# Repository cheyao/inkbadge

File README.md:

# Undercity + Github badges

Official badges for undercity (Hackathon @ Github HQ, https://highway.hackclub.com/)

Find the firmware [here](https://github.com/espcaa/undercity-lanyard)! (Start made by me, finished by spc & mpk :D)

Specs:
- 4x User buttons
- RP2350A
- Big big flash
- Super cool pcie connector
- Working firmware 
- Onboard eink module
- 6 neopixels go flash flash
- Pretty art by bnuuuuyguy!
- Awesome artline by acon (@acornitum)
- Check out pcb online [here](https://kicanvas.org/?github=https%3A%2F%2Fgithub.com%2Fcheyao%2Finkbadge%2Ftree%2Fmain%2Fhardware%2Finkbadge)

Additional battery mode avaliable! (Explosions not included this time)

Solder a lipo onto the central holes on top of the buttons - left is V+ right is GND

Licensed under Solderpad license

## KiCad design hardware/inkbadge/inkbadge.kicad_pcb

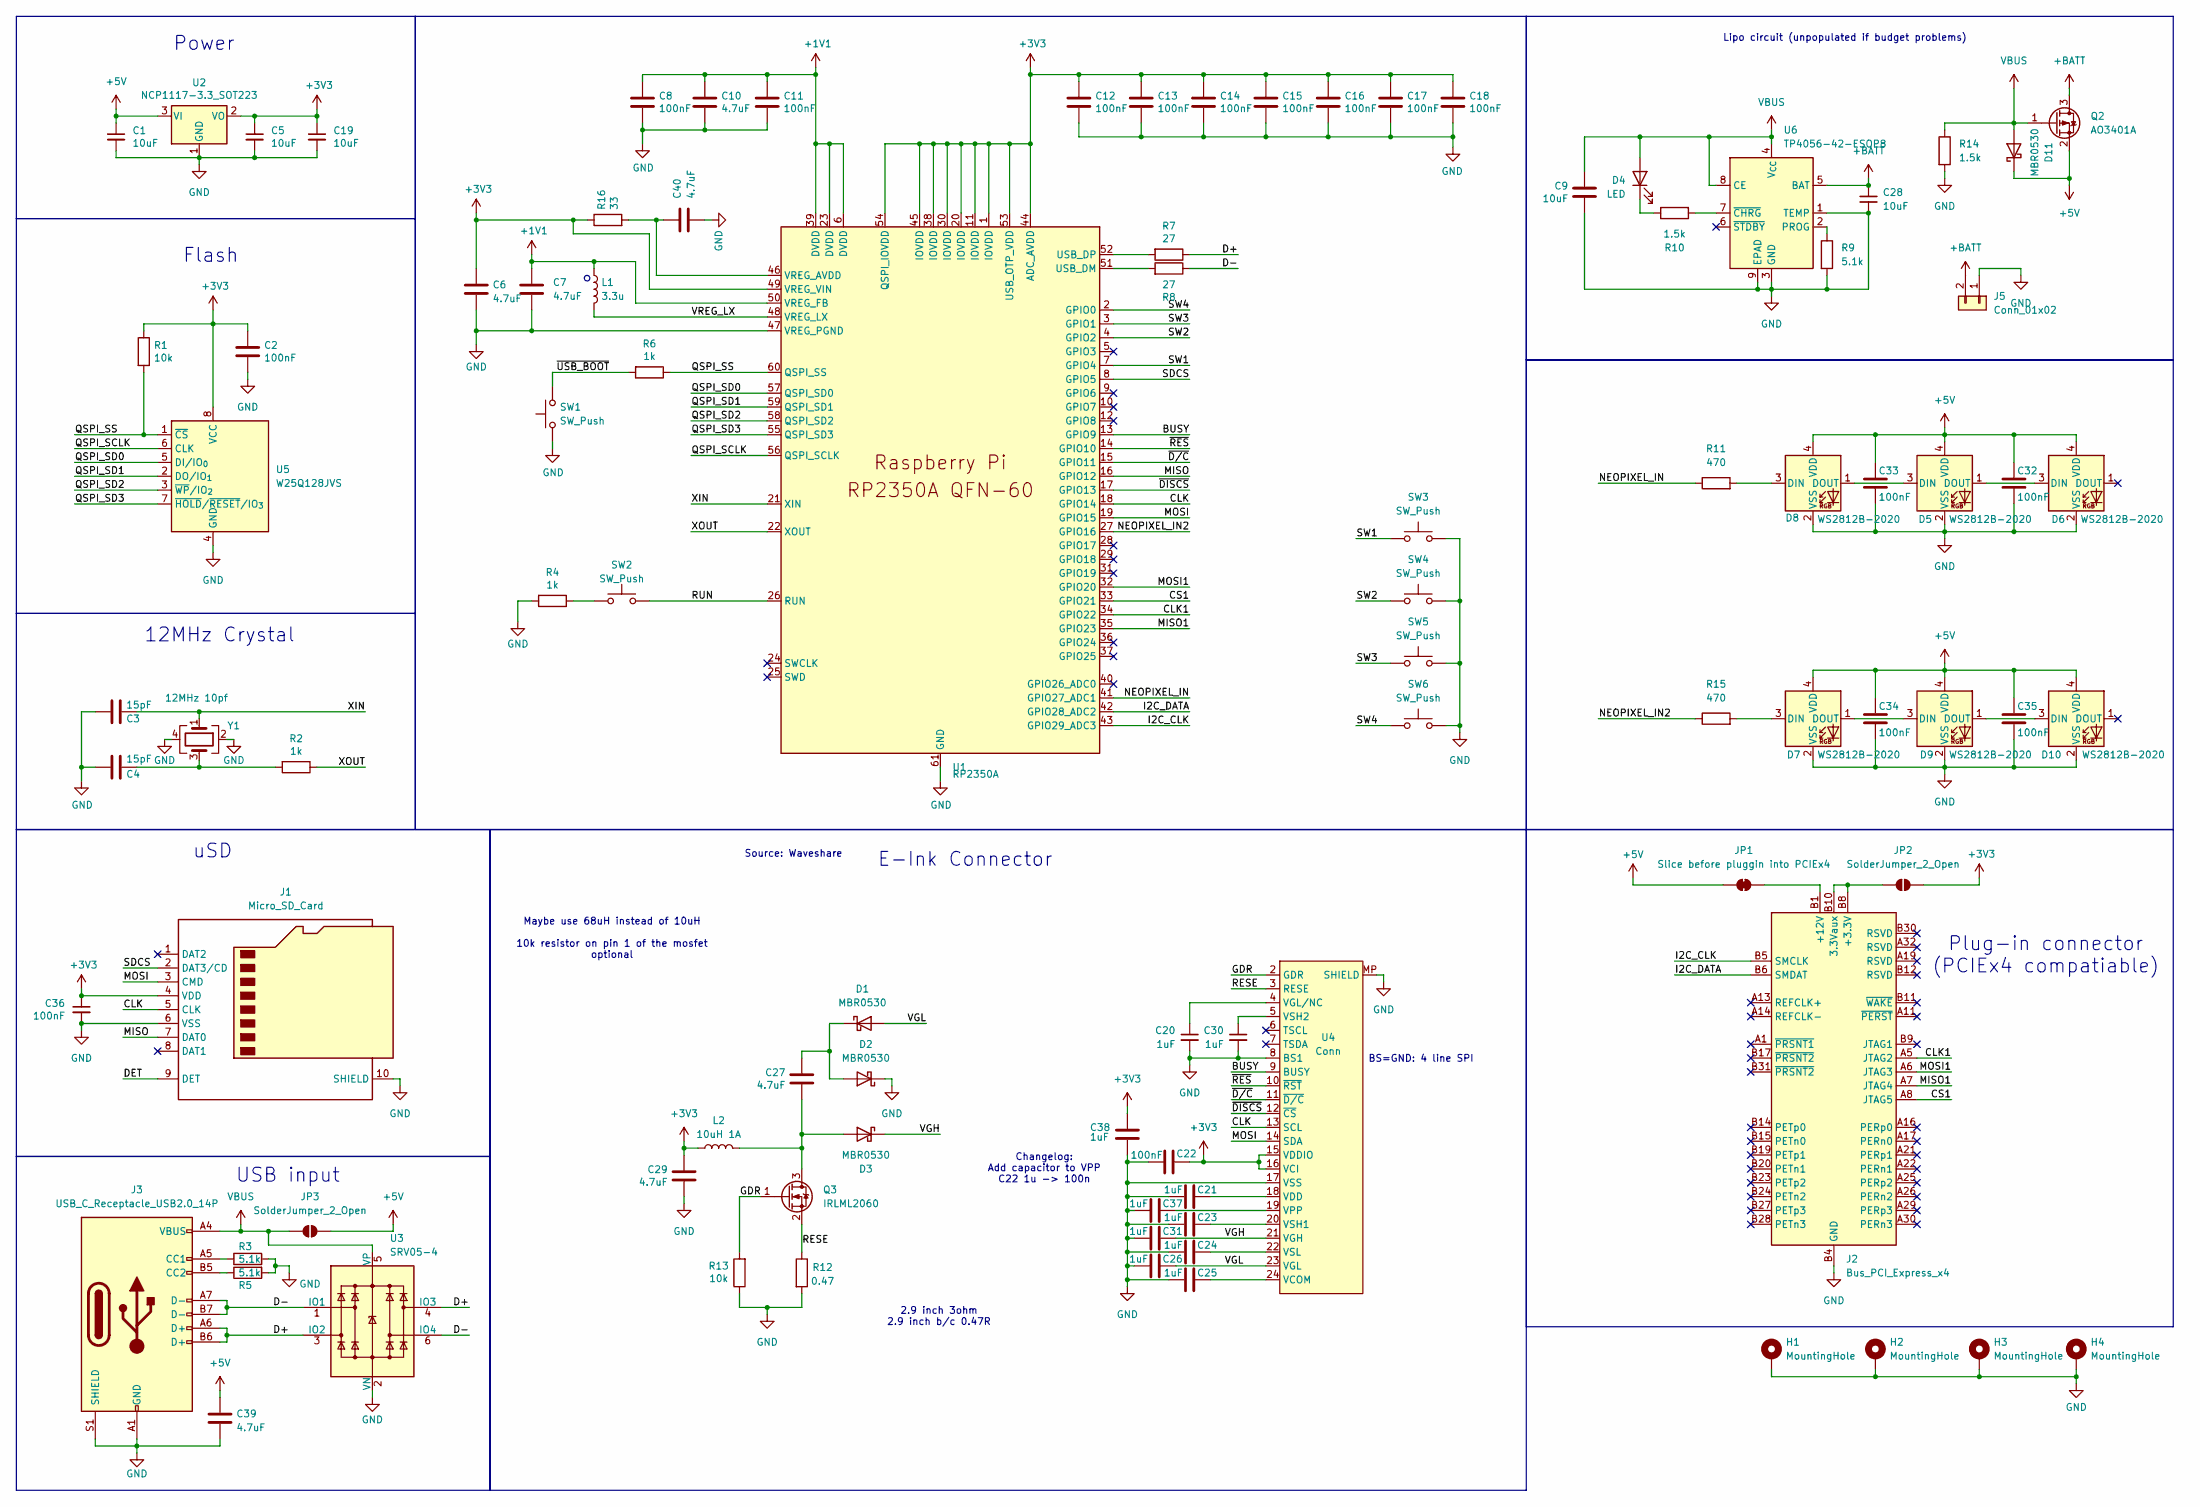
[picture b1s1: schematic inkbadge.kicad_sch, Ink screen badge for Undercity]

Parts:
C1, C5, C9, C19, C28: 10uF; C_0603_1608Metric; LCSC Part # C19702
C2, C8, C11, C12, C13, C14, C15, C16, C17, C18, C22, C32, C33, C34, C35, C36: 100nF; C_0402_1005Metric; LCSC Part # C1525
C3, C4: 15pF; C_0402_1005Metric; LCSC Part # C1548
C6, C7, C10, C40: 4.7uF; C_0402_1005Metric; LCSC Part # C23733
C20, C21, C23, C24, C25, C26, C30, C31, C37, C38: 1uF; C_0402_1005Metric; LCSC Part # C52923
C27, C29, C39: 4.7uF; C_0603_1608Metric; LCSC Part # C69335
D1, D2, D3, D11: MBR0530; D_SOD-123; LCSC Part # C5204746
D4: LED; LED_0603_1608Metric; LCSC Part # C2286
D5, D6, D7, D8, D9, D10: WS2812B-2020; LED_WS2812B-2020_PLCC4_2.0x2.0mm; LCSC Part # C5349955
H1, H2, H3, H4: MountingHole; MountingHole_2.2mm_M2_Pad_Via
J1: Micro_SD_Card; SDCardlcsc; LCSC Part # C5454948
J2: Bus_PCI_Express_x4; BUS_PCIexpress_x4
J3: USB_C_Receptacle_USB2.0_14P; USB_C_Receptacle_GCT_USB4105-xx-A_16P_TopMnt_Horizontal; LCSC Part # C2765186
J5: Conn_01x02; PinHeader_1x02_P2.54mm_Vertical
JP1: Slice before pluggin into PCIEx4; SolderJumper-2_P1.3mm_Bridged_RoundedPad1.0x1.5mm
JP2, JP3: SolderJumper_2_Open; SolderJumper-2_P1.3mm_Open_RoundedPad1.0x1.5mm
L1: 3.3u; L_pol_2016; LCSC Part # C42411119
L2: 10uH 1A; L_APV_ANR4018; LCSC Part # C167808
Q2: AO3401A; SOT-23; LCSC Part # C15127
Q3: IRLML2060; SOT-23; LCSC Part # C5122027
R1, R13: 10k; R_0402_1005Metric; LCSC Part # C25744
R2, R4, R6: 1k; R_0402_1005Metric; LCSC Part # C11702
R3, R5, R9: 5.1k; R_0402_1005Metric; LCSC Part # C25905
R7, R8: 27; R_0402_1005Metric; LCSC Part # C25105
R10, R14: 1.5k; R_0402_1005Metric; LCSC Part # C25867
R11, R15: 470; R_0402_1005Metric; LCSC Part # C25117
R12: 0.47; R_0402_1005Metric; LCSC Part # C3017627
R16: 33; R_0402_1005Metric; LCSC Part # C25105
SW1, SW2, SW3, SW4, SW5, SW6: SW_Push; SW_Push_SPST_TSA016; LCSC Part # C2888430
U1: RP2350A; QFN-60-1EP_7x7mm_P0.4mm_EP3.4x3.4mm_ThermalVias; LCSC Part # C42411118
U2: NCP1117-3.3_SOT223; SOT-223-3_TabPin2; LCSC Part # C6186
U3: SRV05-4; SOT-23-6; LCSC Part # C85364
U4: Conn; LCSC_1x24-1MP_P0.5mm_Horizontal; LCSC Part # C262567
U5: W25Q128JVS; SOIC-8_5.3x5.3mm_P1.27mm; LCSC Part # C97521
U6: TP4056-42-ESOP8; SOP-8_3.9x4.9mm_P1.27mm-TP; LCSC Part # C16581
Y1: 12MHz 10pf; Crystal_SMD_3225-4Pin_3.2x2.5mm; LCSC Part # C20625731

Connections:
+1V1: C7.1, C8.1, C10.1, C11.1, L1.1, U1.6 (DVDD), U1.23 (DVDD), U1.39 (DVDD), U1.50 (VREG_FB)
+3V3: C2.1, C5.1, C6.1, C12.1, C13.1, C14.1, C15.1, C16.1, C17.1, C18.1, C19.1, C22.1, C29.1, C36.1, C38.1, J1.4 (VDD), JP2.2 (B), L2.1, R1.1, R16.1, U1.1 (IOVDD), U1.11 (IOVDD), U1.20 (IOVDD), U1.30 (IOVDD), U1.38 (IOVDD), U1.44 (ADC_AVDD), U1.45 (IOVDD), U1.49 (VREG_VIN), U1.53 (USB_OTP_VDD), U1.54 (QSPI_IOVDD), U2.2 (VO), U4.15 (VDDIO), U4.16 (VCI), U5.8 (VCC)
+5V: C1.1, C32.1, C33.1, C34.1, C35.1, C39.1, D5.4 (VDD), D6.4 (VDD), D7.4 (VDD), D8.4 (VDD), D9.4 (VDD), D10.4 (VDD), D11.1 (K), JP1.1 (A), JP3.2 (B), Q2.2 (S), U2.3 (VI)
+BATT: C28.1, J5.2, Q2.3 (D), U6.5 (BAT)
/BUSY: U1.13 (GPIO9), U4.9 (BUSY)
/CLK: J1.5 (CLK), U1.18 (GPIO14), U4.13 (SCL)
/CLK1: J2.A5 (JTAG2), U1.34 (GPIO22)
/CS1: J2.A8 (JTAG5), U1.33 (GPIO21)
/D+: J3.A6 (D+), J3.B6 (D+), R7.1, U3.3 (IO2), U3.4 (IO3)
/D-: J3.A7 (D-), J3.B7 (D-), R8.1, U3.1 (IO1), U3.6 (IO4)
/DET: J1.9 (DET)
/GDR: Q3.1 (G), R13.2, U4.2 (GDR)
/I2C_CLK: J2.B5 (SMCLK), U1.43 (GPIO29_ADC3)
/I2C_DATA: J2.B6 (SMDAT), U1.42 (GPIO28_ADC2)
/MISO: J1.7 (DAT0), U1.16 (GPIO12)
/MISO1: J2.A7 (JTAG4), U1.35 (GPIO23)
/MOSI: J1.3 (CMD), U1.19 (GPIO15), U4.14 (SDA)
/MOSI1: J2.A6 (JTAG3), U1.32 (GPIO20)
/NEOPIXEL_IN: R11.1, U1.41 (GPIO27_ADC1)
/NEOPIXEL_IN2: R15.1, U1.27 (GPIO16)
/QSPI_SCLK: U1.56 (QSPI_SCLK), U5.6 (CLK)
/QSPI_SD0: U1.57 (QSPI_SD0), U5.5 (DI/IO_{0})
/QSPI_SD1: U1.59 (QSPI_SD1), U5.2 (DO/IO_{1})
/QSPI_SD2: U1.58 (QSPI_SD2), U5.3 (~WP/IO_{2})
/QSPI_SD3: U1.55 (QSPI_SD3), U5.7 (~HOLD/~RESET/IO_{3})
/QSPI_SS: R1.2, R6.1, U1.60 (QSPI_SS), U5.1 (~CS)
/RESE: Q3.2 (S), R12.1, U4.3 (RESE)
/RUN: SW2.2, U1.26 (RUN)
/SDCS: J1.2 (DAT3/CD), U1.8 (GPIO5)
/SW1: SW3.1, U1.7 (GPIO4)
/SW2: SW4.1, U1.4 (GPIO2)
/SW3: SW5.1, U1.3 (GPIO1)
/SW4: SW6.1, U1.2 (GPIO0)
/VGH: C31.1, D3.1 (K), U4.21 (VGH)
/VGL: C26.1, D1.2 (A), U4.23 (VGL)
/VREG_LX: L1.2, U1.48 (VREG_LX)
/XIN: C3.1, U1.21 (XIN), Y1.1
/XOUT: R2.1, U1.22 (XOUT)
/~DISCS: U1.17 (GPIO13), U4.12 (~CS)
/~D/C: U1.15 (GPIO11), U4.11 (~D/C)
/~RES: U1.14 (GPIO10), U4.10 (~RST)
/~USB_BOOT: R6.2, SW1.2
GND: C1.2, C2.2, C3.2, C4.2, C5.2, C6.2, C7.2, C8.2, C9.2, C10.2, C11.2, C12.2, C13.2, C14.2, C15.2, C16.2, C17.2, C18.2, C19.2, C20.2, C21.2, C22.2, C23.2, C24.2, C25.2, C26.2, C28.2, C29.2, C30.2, C31.2, C32.2, C33.2, C34.2, C35.2, C36.2, C37.2, C38.2, C39.2, C40.2, D2.1 (K), D5.2 (VSS), D6.2 (VSS), D7.2 (VSS), D8.2 (VSS), D9.2 (VSS), D10.2 (VSS), H1.1, H2.1, H3.1, H4.1, J1.6 (VSS), J1.10 (SHIELD), J2.A4 (GND), J2.A12 (GND), J2.A15 (GND), J2.A18 (GND), J2.A20 (GND), J2.A23 (GND), J2.A24 (GND), J2.A27 (GND), J2.A28 (GND), J2.A31 (GND), J2.B4 (GND), J2.B7 (GND), J2.B13 (GND), J2.B16 (GND), J2.B18 (GND), J2.B21 (GND), J2.B22 (GND), J2.B25 (GND), J2.B26 (GND), J2.B29 (GND), J2.B32 (GND), J3.A1 (GND), J3.A12 (GND), J3.B1 (GND), J3.B12 (GND), J3.S1 (SHIELD), J5.1, R3.2, R4.2, R5.2, R9.2, R12.2, R13.1, R14.2, SW1.1, SW3.2, SW4.2, SW5.2, SW6.2, U1.47 (VREG_PGND), U1.61 (GND), U2.1 (GND), U3.2 (VN), U4.8 (BS1), U4.17 (VSS), U4.MP (SHIELD), U5.4 (GND), U6.1 (TEMP), U6.3 (GND), U6.9 (EPAD), Y1.2, Y1.4
unnamed: C4.1, R2.2, Y1.3
unnamed: C27.1, D1.1 (K), D2.2 (A)
unnamed: C27.2, D3.2 (A), L2.2, Q3.3 (D)
unnamed: D4.1 (K), R10.1
unnamed: D5.3 (DIN), D8.1 (DOUT)
unnamed: D5.1 (DOUT), D6.3 (DIN)
unnamed: D7.3 (DIN), R15.2
unnamed: D7.1 (DOUT), D9.3 (DIN)
unnamed: D8.3 (DIN), R11.2
unnamed: D9.1 (DOUT), D10.3 (DIN)
unnamed: J2.A9 (+3.3V), J2.A10 (+3.3V), J2.B8 (+3.3V), J2.B10 (3.3Vaux), JP2.1 (A)
unnamed: J3.A5 (CC1), R3.1
unnamed: J3.B5 (CC2), R5.1
unnamed: J2.A2 (+12V), J2.A3 (+12V), J2.B1 (+12V), J2.B2 (+12V), J2.B3 (+12V), JP1.2 (B)
unnamed: R4.1, SW2.1
unnamed: R8.2, U1.51 (USB_DM)
unnamed: R7.2, U1.52 (USB_DP)
unnamed: C40.1, R16.2, U1.46 (VREG_AVDD)
unnamed: C25.1, U4.24 (VCOM)
unnamed: C21.1, U4.18 (VDD)
unnamed: C20.1, U4.4 (VGL/NC)
unnamed: C37.1, U4.19 (VPP)
unnamed: C23.1, U4.20 (VSH1)
unnamed: C30.1, U4.5 (VSH2)
unnamed: C24.1, U4.22 (VSL)
unnamed: R9.1, U6.2 (PROG)
unnamed: R10.2, U6.7 (~CHRG)
VBUS: C9.1, D4.2 (A), D11.2 (A), J3.A4 (VBUS), J3.A9 (VBUS), J3.B4 (VBUS), J3.B9 (VBUS), JP3.1 (A), Q2.1 (G), R14.1, U3.5 (VP), U6.4 (V_{CC}), U6.8 (CE)

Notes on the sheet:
USB input
Maybe use 68uH instead of 10uH 10k resistor on pin 1 of the mosfet optional
Plug-in connector (PCIEx4 compatiable)
Changelog: Add capacitor to VPP C22 1u -> 100n
Lipo circuit (unpopulated if budget problems)
Flash
2.9 inch 3ohm 2.9 inch b/c 0.47R
BS=GND: 4 line SPI
uSD
Source: Waveshare
12MHz Crystal
Power
E-Ink Connector

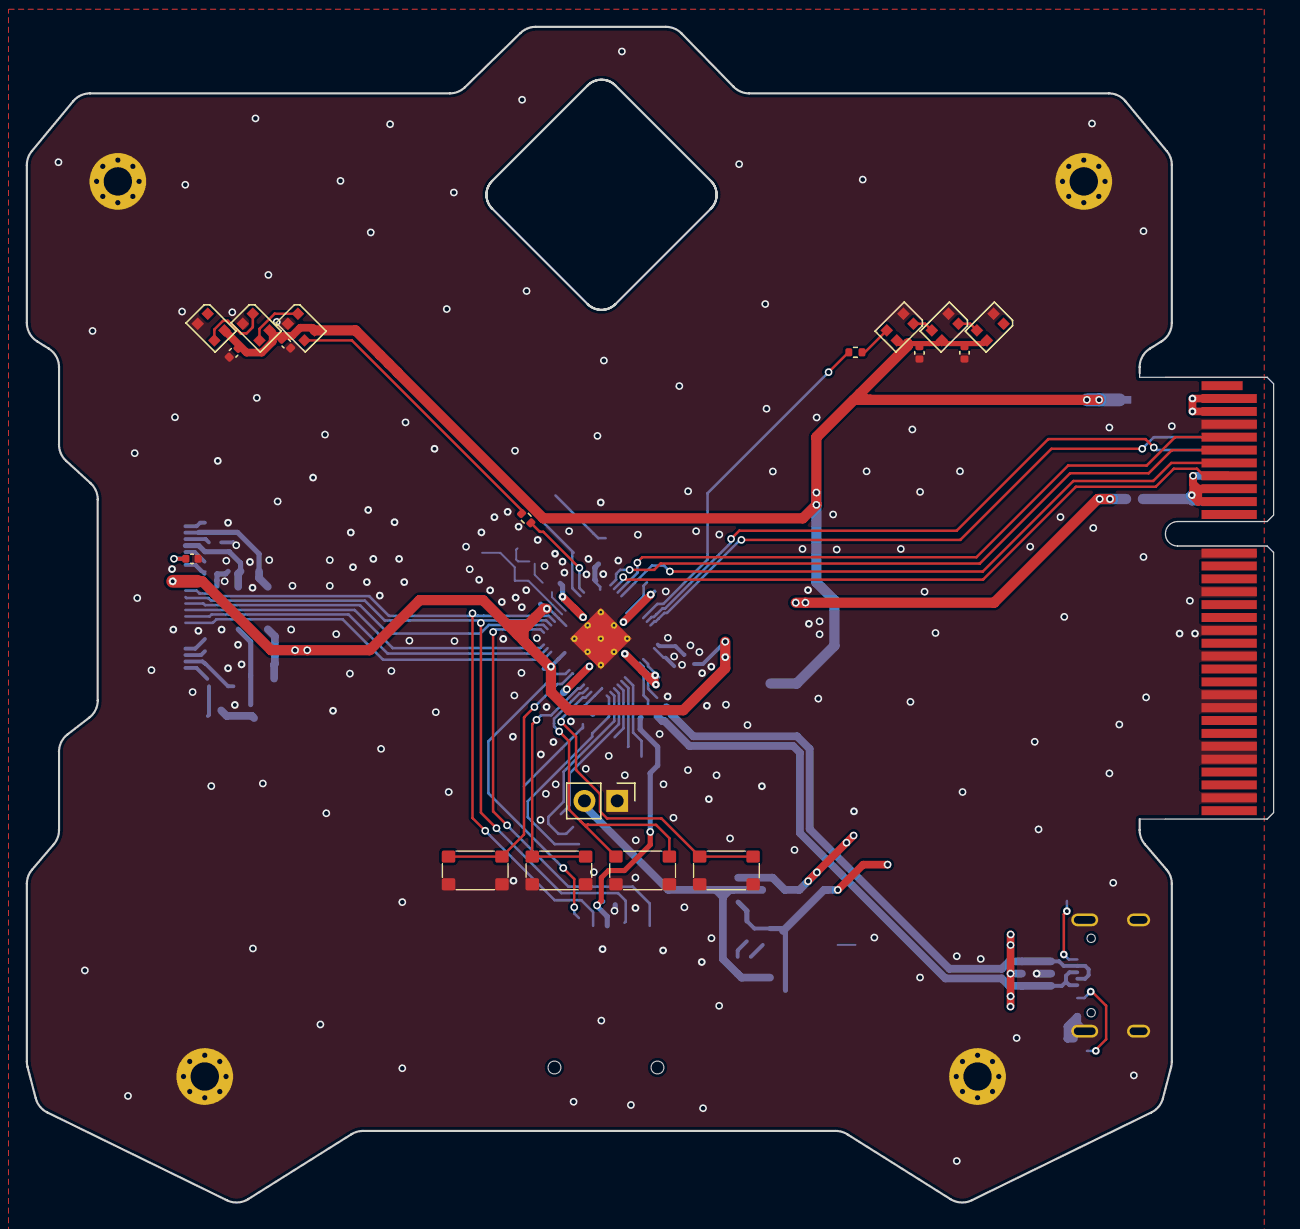
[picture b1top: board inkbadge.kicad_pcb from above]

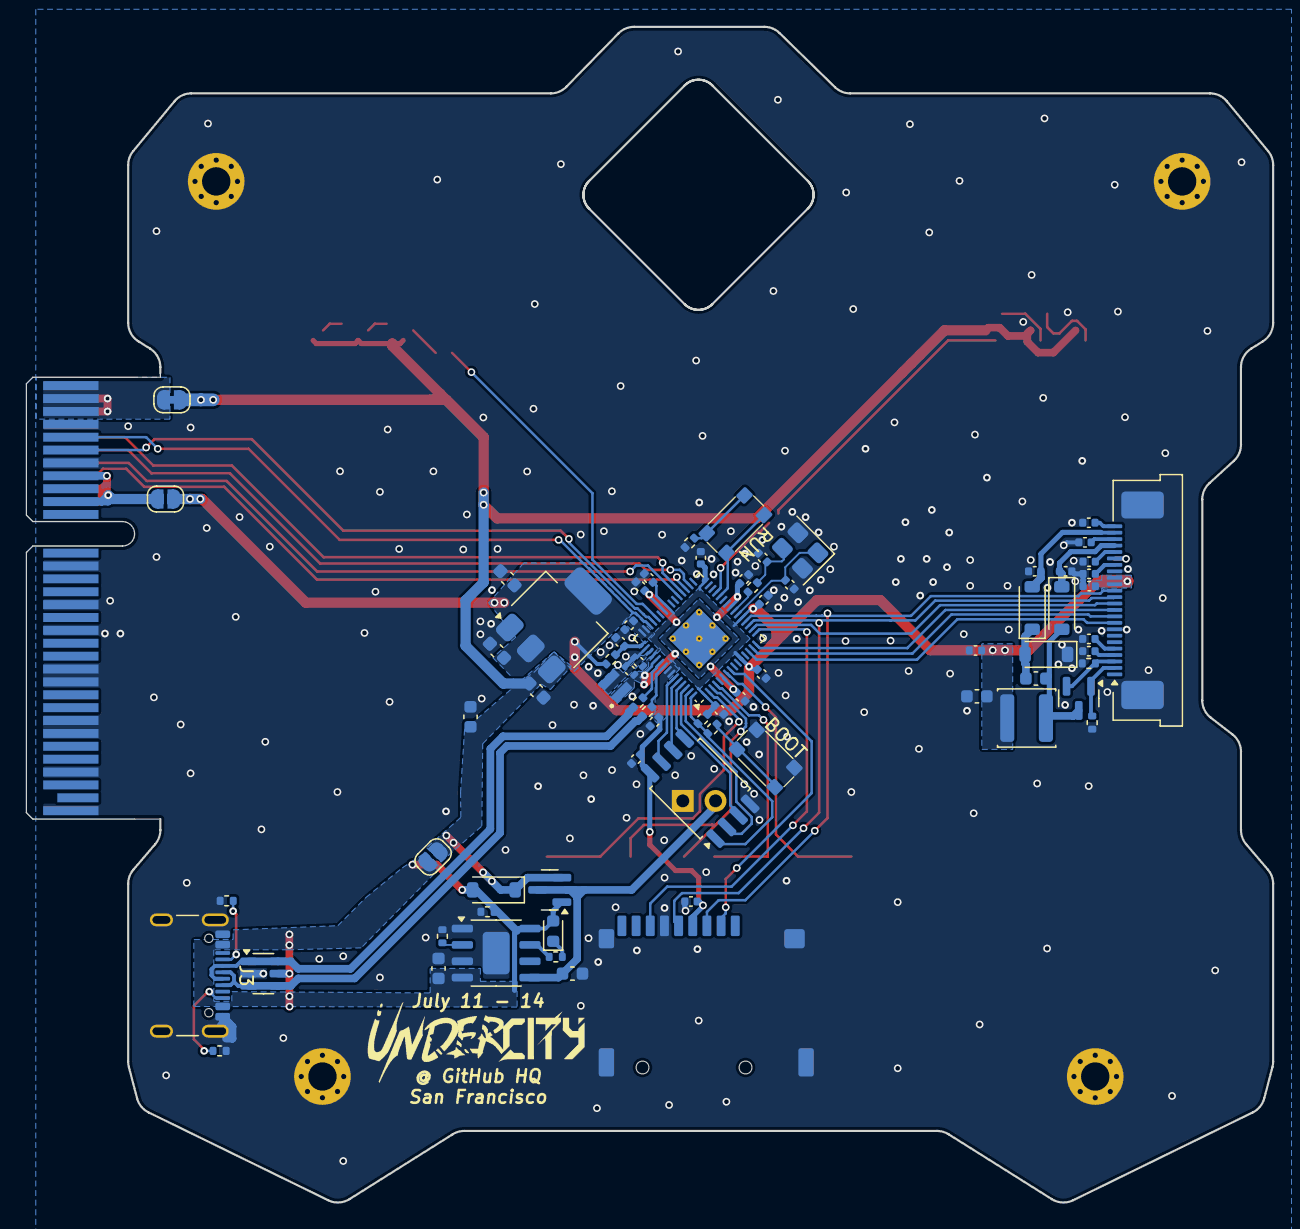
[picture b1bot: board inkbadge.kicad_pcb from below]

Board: 2 copper layers, 96.8 x 91.3 mm, 95 parts (73 on the bottom side), 70 nets.

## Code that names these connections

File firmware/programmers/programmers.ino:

/*
  Hack Club Undercity badge firmware
  Credit: 

  The circuit according to the badge schematic:
   SD card attached to SPI bus on rp2350:
   ************ SPI0 ************
   ** MISO (AKA RX) - gpio12
   ** MOSI (AKA TX) - gpio15
   ** CS            - gpio5
   ** SCK           - gpio14

  Eink Display attached to SPI bus on rp2350:
   ************ SPI0 ************
   ** MISO (AKA RX) - gpio12
   ** MOSI (AKA TX) - gpio15
   ** CS            - gpio5
   ** SCK           - gpio14

*/

/*
    *** DEPENDENCIES ***

  - arduino SPI
  - adafruit SD 
  - earlphilehower arduino-pico
  - adafruit EPD
  - adafruit ImageReader
*/

// This are GP pins for SPI on the Raspberry Pi Pico board, and connect
// to different *board* level pinouts.  Check the PCB while wiring.
// Only certain pins can be used by the SPI hardware, so if if you change
// these be sure they are legal or the program will crash.
//
constexpr const int _MISO_SD = 20;  // Changed to gpio12 as per schematic
constexpr const int _CS_SD = 21;
constexpr const int _SCK_SD = 22;   // Changed to gpio14 as per schematic
constexpr const int _MOSI_SD = 23;  // Changed to gpio15 as per schematic


// Programma! SPI1
constexpr const int _MISO_PGM = 8;
constexpr const int _CS_PGM = 9;
constexpr const int _CLK_PGM = 10;
constexpr const int _MOSI_PGM = 11;

#include <SPI.h>
#include <SdFat_Adafruit_Fork.h>

SPISettings spisettings(1000000, MSBFIRST, SPI_MODE0);
SdFat SD;

#define SD_CONFIG SdSpiConfig(_CS_SD, SHARED_SPI, SD_SCK_MHZ(1000000), &SPI1)

void setup() {
  // Open serial communications and wait for port to open
  Serial.begin(115200);

  while (!Serial) {
    delay(1); // wait for serial port to connect. Needed for native USB port only (aka the rp2350 i think maybe, idk it was in the example rp2350 code)
  }

  Serial.println("\nInitializing SD card...");

  // Set up SPI pins for the SD card
  SPI1.setMISO(_MISO_SD);
  SPI1.setMOSI(_MOSI_SD);
  SPI1.setSCK(_SCK_SD);
  SPI1.setCS(_CS_SD);

  if (!SD.begin(SD_CONFIG)) {
    Serial.println("SD initialization failed!");
  } else {
    Serial.println("SD initialization done.");
  }

  pinMode(_MISO_PGM, INPUT_PULLDOWN);

  SPI.setTX(_MISO_PGM);
  SPI.setRX(_MOSI_PGM);
  SPI.setSCK(_CLK_PGM);
  SPI.setCS(_CS_PGM);

  SPI.begin();
}

bool flashed = false;

void loop() {
  auto i = digitalRead(_MISO_PGM);
  if (i == HIGH) {
    // Start transaction
    char* name = "Cyao";
    SPI.transfer(static_cast<void*>(name), strlen(name) + 1);
  } else {
    // No badge
    flashed = true;
  }

  delay(300);
}

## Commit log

2025-05-30 Init
2025-05-31 Progress
2025-06-07 Journaling
2025-06-19 Badge like done!
2025-06-20 Finish programmer
2025-06-24 PUSH
2025-07-11 SOME FIRMWARE IG FAQ THE WORLD IDC ME DIE
2025-07-11 README
2025-07-11 FIRMWARE
2025-07-11 FIRMWARE IDKFHRGVKQHBJ
2025-07-11 WORK?
2025-07-11 THING
2026-01-22 Fix broken CDN links
2026-06-11 Remove ugly eagle syms
